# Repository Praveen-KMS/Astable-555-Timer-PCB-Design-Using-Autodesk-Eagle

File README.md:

# Astable-555-Timer-PCB-Design-Using-Autodesk-Eagle

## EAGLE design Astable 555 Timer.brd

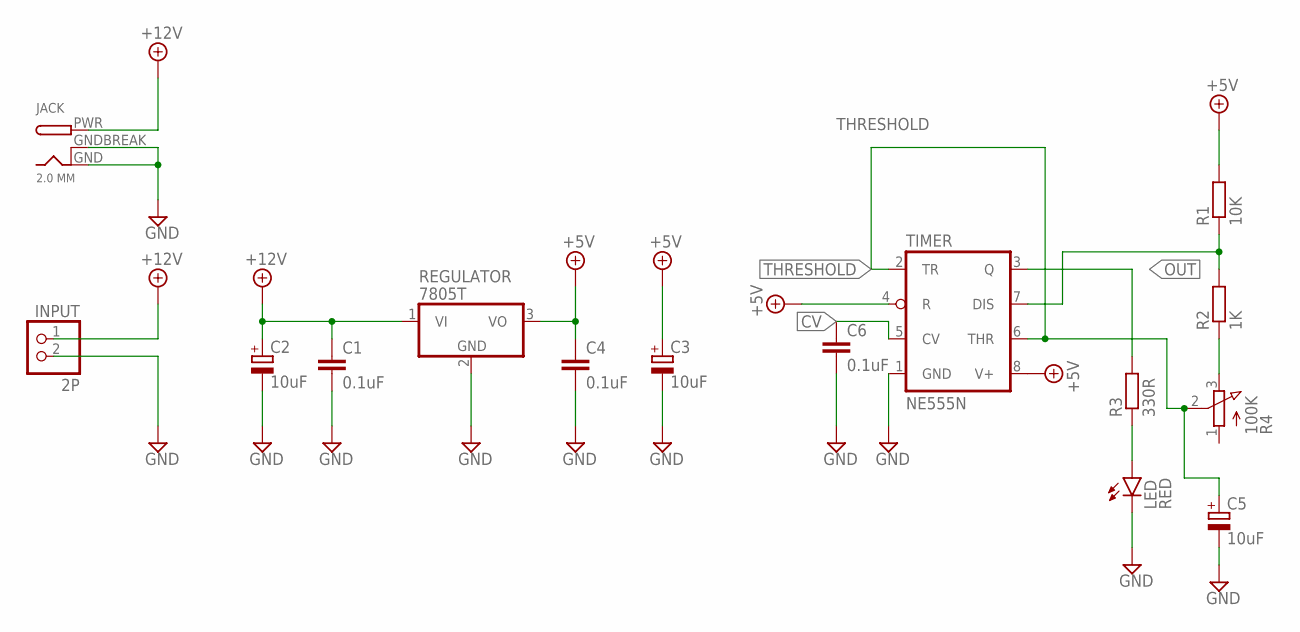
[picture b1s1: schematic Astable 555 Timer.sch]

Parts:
C1, C4, C6: 0.1uF; C050-030X075
C2, C3, C5: 10uF; E3,5-8
INPUT: 2P; 1X02
JACK: 2.0 MM; DCJACK_2MM_PTH
LED: RED; LED5MM
R1: 10K; 0207/10
R2: 1K; 0207/10
R3: 330R; 0207/10
R4: 100K; 3RP/1610N
REGULATOR: 7805T; TO220H
TIMER: NE555N; DIL08

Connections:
+5V: C3.+, C4.1, R1.2, REGULATOR.3 (VO), TIMER.4 (R), TIMER.8 (V+)
+12V: C1.1, C2.+, INPUT.1, JACK.PWR, REGULATOR.1 (VI)
CV: C6.1, TIMER.5 (CV)
GND: C1.2, C2.-, C3.-, C4.2, C5.-, C6.2, INPUT.2, JACK.GND, JACK.GNDBREAK, LED.K (C), REGULATOR.2 (GND), TIMER.1 (GND)
unnamed: R1.1, R2.2, TIMER.7 (DIS)
unnamed: R2.1, R4.3 (E)
unnamed: LED.A, R3.1
OUT: R3.2, TIMER.3 (Q)
THRESHOLD: C5.+, R4.2 (S), TIMER.2 (TR), TIMER.6 (THR)

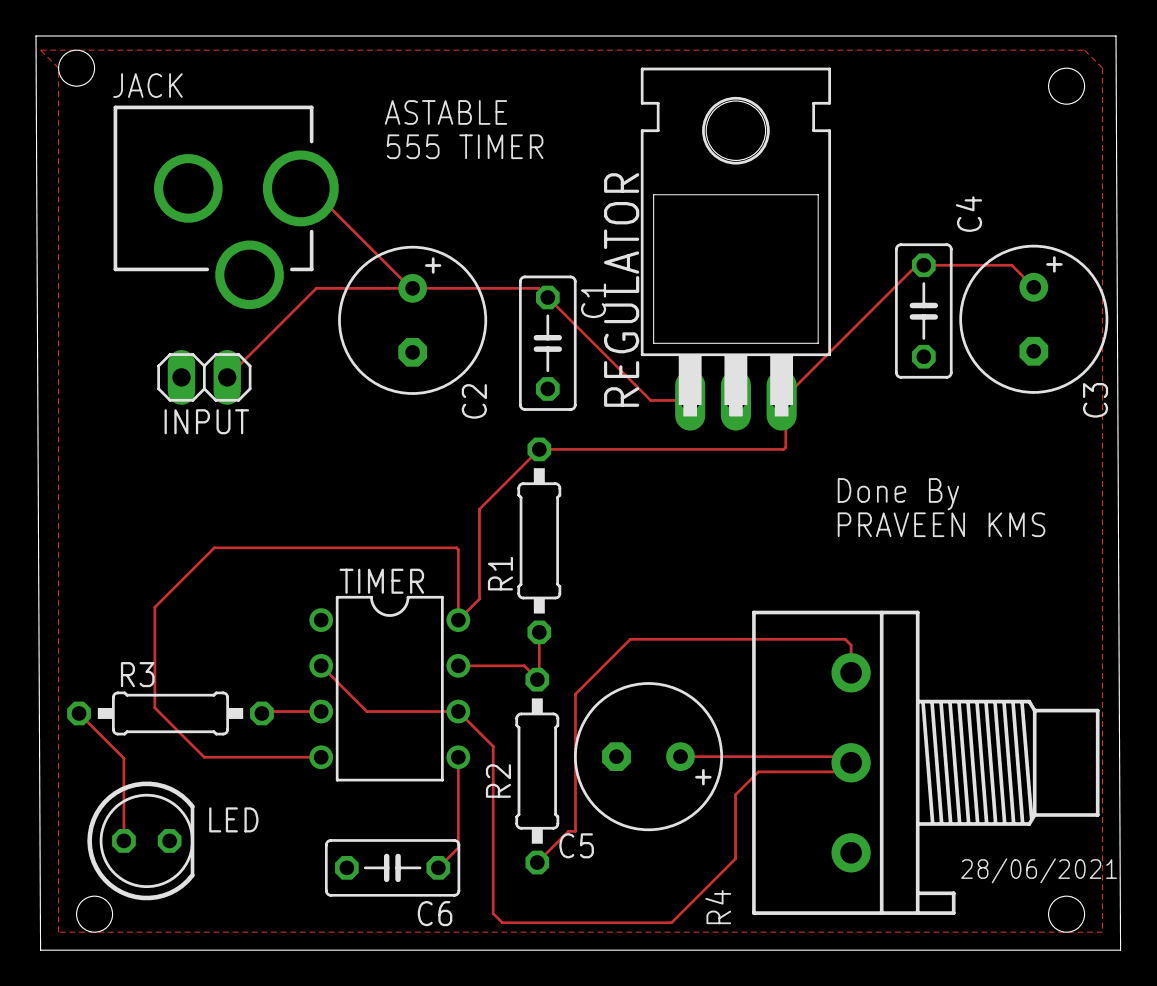
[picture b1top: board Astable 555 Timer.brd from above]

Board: 2 copper layers, 60.3 x 50.8 mm, 15 parts (0 on the bottom side), 9 nets.
